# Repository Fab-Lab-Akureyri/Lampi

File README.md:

# Lampi

## Markmið

Búa til lítinn og skrítinn lampa sem kennsluefni í Fab Lab. 

## Íhlutir
- [Seeed Xiao RP2040](https://www.seeedstudio.com/XIAO-RP2040-v1-0-p-5026.html)
- [Neopixel hringur (12LED, RGBW)](https://www.adafruit.com/product/2852) 
- 2 [takkar](https://www.digikey.com/en/products/detail/omron-electronics-inc-emc-div/B3SN-3112P/27856)
- 2 [499Ω smd viðnám](https://www.digikey.com/en/products/detail/yageo/RC1206FR-07499RL/728944)
- PCB bretti
- 2.9mm x ___ skrúfa

## Uppsetning
- Sækja [Circuitpython](https://circuitpython.org/board/seeeduino_xiao_rp2040/) firmware, 9. útgáfu - (einnig hér í repo-inu). 
- Setja Circuitpython upp á RP2040, [sjá leiðbeiningar](https://wiki.seeedstudio.com/XIAO-RP2040-with-CircuitPython/)
- Setja `code.py` í rótina á RP2040. 
- Setja `lib` möppuna á rótina á RP2040.

## Rafmagnsteikningar

## Þrívíddarmódel 

- [Skel](/model/Skel.stl)

- [Botn](/model/Botn.stl)

- [Skermur](/model/Skermur.stl)

## Brettið

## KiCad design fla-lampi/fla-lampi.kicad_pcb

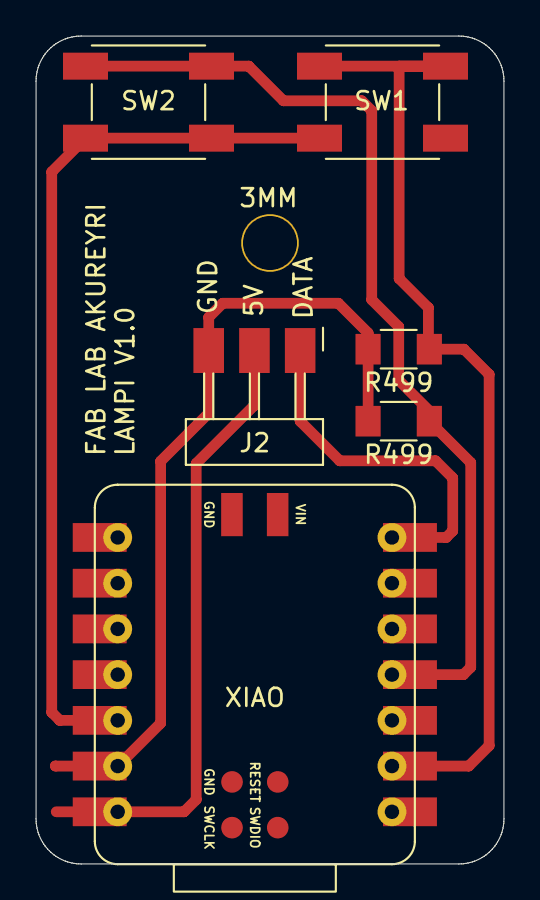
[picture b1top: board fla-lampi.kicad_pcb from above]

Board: 2 copper layers, 26.0 x 46.0 mm, 6 parts (0 on the bottom side), 6 nets.

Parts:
J2: Conn_PinHeader_1x03_P2.54mm_Horizontal_SMD; PinHeader_1x03_P2.54mm_Horizontal_SMD
R499, R499#2: R499; R_1206
SW1, SW2: BUTTON_B3SN; Button_Omron_B3SN_6.0x6.0mm
XIAO: Module_XIAO-RP2040; SeeedStudio_XIAO_RP2040

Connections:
A1: R499.1, SW1.1, XIAO.2 (D1)
A3: R499#2.1, SW2.1, XIAO.4 (D3)
A6: J2.1, XIAO.7 (D6)
GND: J2.3, R499.2, R499#2.2, XIAO.13 (GND)
PWR_3V3: SW1.2, SW2.2, XIAO.12 (3V3)
PWR_5V: J2.2, XIAO.14 (5V)

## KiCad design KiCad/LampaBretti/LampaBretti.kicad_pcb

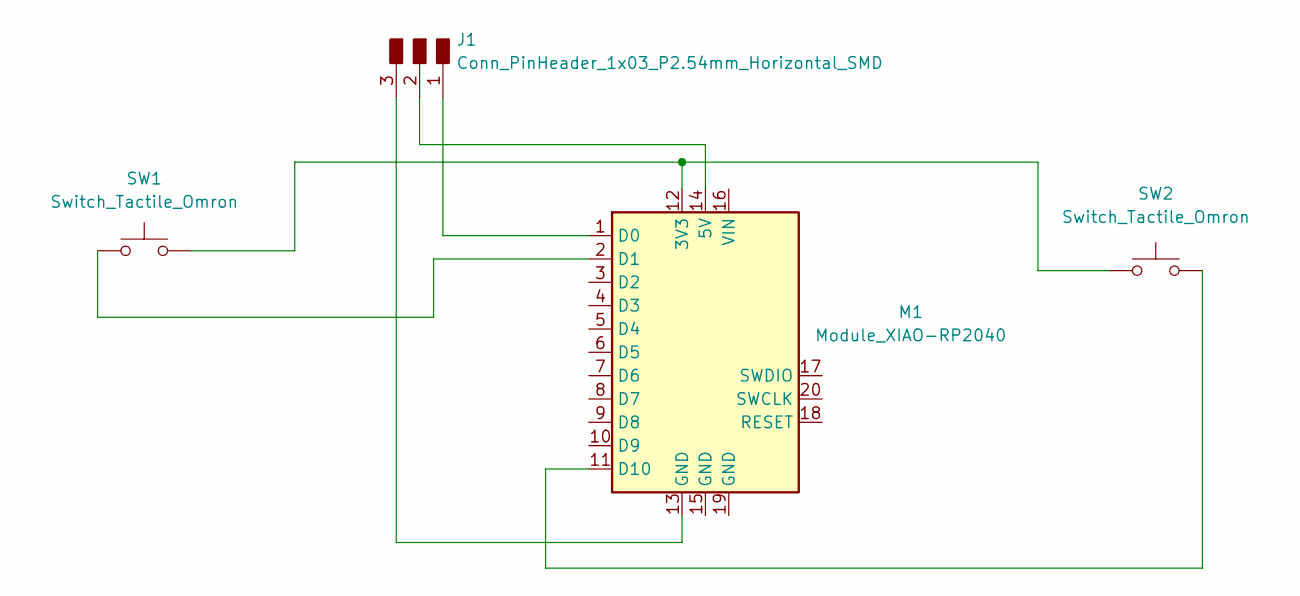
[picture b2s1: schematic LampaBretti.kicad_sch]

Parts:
J1: Conn_PinHeader_1x03_P2.54mm_Horizontal_SMD; PinHeader_1x03_P2.54mm_Horizontal_SMD
M1: Module_XIAO-RP2040; SeeedStudio_XIAO_RP2040
SW1, SW2: Switch_Tactile_Omron; Button_Omron_B3SN_6.0x6.0mm

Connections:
unnamed: J1.1, M1.1 (D0)
unnamed: J1.2, M1.14 (5V)
unnamed: J1.3, M1.13 (GND)
unnamed: M1.12 (3V3), SW1.2, SW2.2
unnamed: M1.2 (D1), SW1.1
unnamed: M1.11 (D10), SW2.1

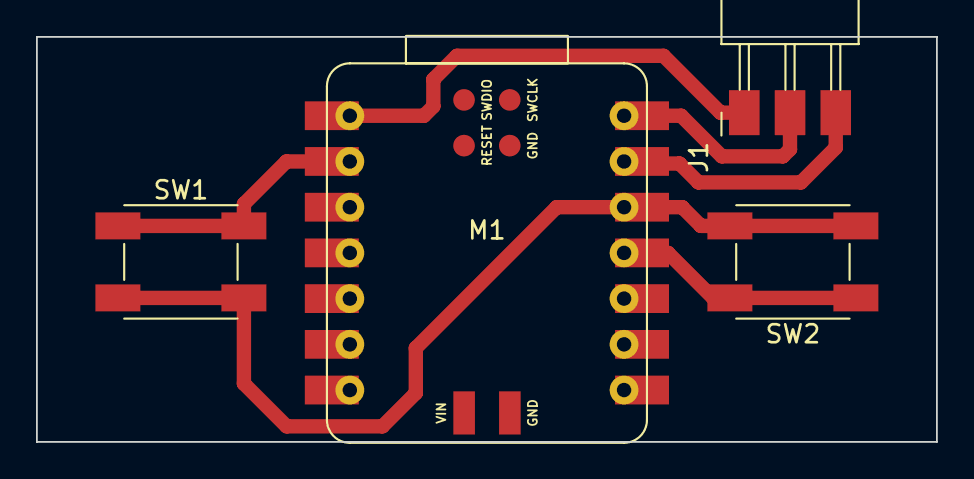
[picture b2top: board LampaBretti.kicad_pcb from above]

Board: 2 copper layers, 50.0 x 22.5 mm, 4 parts (0 on the bottom side), 6 nets.

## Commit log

2023-10-17 Added example webserver with bootstrap
2023-10-17 Two folders
2023-10-18 Eitthvað test
2023-10-19 Added lampi.io - platformio, spiffs working
2023-10-19 esp32c3 + https://github.com/me-no-dev/ESPAsyncWebServer/pull/1142#pullrequestreview-1484108936 : working
2023-10-19 Bætti við í readme
2023-10-19 Added neopixel library. Onboard diode working with default html
2023-10-19 Íslenskir stafir OK, laga api path
2023-10-19 Get neopixel working
2023-10-19 RGB colors working
2023-10-19 servo working
2023-10-19 Servo control og ui update
2023-10-19 Bætti við myndum
2023-10-19 Screenshot
2023-10-19 Tiltekt
2023-10-19 Skref, readme
2023-10-19 more responsive
2023-10-22 hyperlinks
2023-10-22 apsalut link
2023-10-22 link fix
2023-10-23 Bootstrap 5
2023-10-23 link and text update
2023-10-25 Bootstrap 5 instead of custom css
2023-10-25 Color picker
2023-10-25 Relax mode added
2023-10-26 Added mdsn
2023-11-01 Cleanup, removed servo completely
2023-11-01 Brightness slider
2023-11-01 White part of the RGBW implemented
2023-11-01 Moved .io into root dir and added config.h for wifi setup
2023-11-01 Added rest of .io
2023-11-01 Added config.h to .gitignore
2023-11-01 ignore testing
2023-11-01 Changed config to template
2023-11-01 Slider, full width
2023-11-02 Brightness fix
2023-11-15 Breytti Neopixel pinna úr D1 -> D0
2023-11-15 Myndir
2023-11-15 Readme
2023-12-20 Bætti við bretti
2024-01-19 Added 2btn pcb & circuitpython code
2024-01-25 Update circuitpython code
2024-01-26 Added circuitpython 8 uf2 file and needed libraries
2024-01-29 Bretti
2024-01-29 Fjarlægði eldra bretti
2024-01-30 update ignore
2024-01-31 Update pinout and project
2024-02-07 .\circuitpython\code.py
2024-09-13 Added svg
2024-09-18 prod
2024-09-26 Added stuff
2024-09-28 remove extensions.json
2024-09-28 ignore vscode folder
2024-09-28 Seprate branch for es32c3 version
2024-09-28 Tiltekt a main
2024-09-28 M->m
2024-09-28 Brettid
2024-11-01 Added production zip
2024-11-05 Cleanup
2025-01-15 FW 8 -> 9
